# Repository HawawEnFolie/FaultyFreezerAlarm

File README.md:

# Faulty Ultralow-temperature Freezer Alarm

## ⟪ DESCRIPTION ⟫

This repository contains the source code and documentation for a critical telemetry embedded system. Developed during the first year of the BTS CIEL ER program to meet the needs of the UPPA (University de Pau et des Pays de l'Adour) microbiology laboratories, this system monitors the temperature of ultra-low temperature freezers in real time. If the temperature crosses a critical threshold, here -65°C, the system triggers an immediate SMS alert via a 4G LTE cellular network to designated rsearchers so as to reduce as much as possible the time where samples are not correctly frozen.

## ⟪ FEATURES ⟫

**▰ High-Precision Acquisition ⪢** Temperature reading every 10 minutes via an industrial PT100 probe and a MAX31865 amplifier (SPI communication).

**▰ Cellular Connectivity ⪢** Automated messages sent over the mobile data network directly to a WhatsApp group using an HTTP API gateway on a SIMCom A7670E module

**▰ Anti-Spam Logic ⪢** The system includes a software lock to send only one SMS when the threshold is crossed, automatically resetting once the temperature stabilizes below a set level, so as not a flood the target phones with multiple SMS.

**▰ Local Monitoring ⪢** Real-time display of readings and network status on the serial monitor with integrated DEBUG mode as well as screen to show live info about the PT100.

**▰ Ambient Temperature Tracking ⪢** Continuous measurement of the ambient room temperature utilizing a TMP102 sensor.

**▰ Local Alerts & Interface ⪢** An integrated buzzer for immediate audible alarms and an SSD1315 OLED display equipped with 4 integrated buttons for local navigation and control.

## ⟪ HARDWARE REQUIREMENTS ⟫

**▰ Microcontroller & Modem ⪢** LilyGo T-A7670E development board (Based on an ESP32-WROVER with an integrated 4G LTE modem).

**▰ RTD Amplifier ⪢** Adafruit MAX31865 module.

**▰ Sensor ⪢** PT100 temperature probe with 4 wires (can be configured for 2 and 3 wires as well).

**▰ Additional Peripherals ⪢** TMP102 ambient temperature sensor, alert buzzer, and an SSD1315 OLED display module with 4 built-in buttons.

**▰ Power & Connectivity ⪢** Active SIM card (with SMS plan) and suitable power supply for the LilyGo board.

## ⟪ SOFTWARE REQUIREMENTS ⟫

**▰ IDE ⪢** Visual Studio Code with the PlatformIO extension.

**▰ Framework ⪢** Arduino (C++).

## [ Dependencies & Libraries ]

**▰** Adafruit MAX31865 library (Handling of the sensor's analog-to-digital conversion).

**▰** TinyGSM (Seamless handling of AT commands and communication with the SIMCom modem).

## ⟪ LICENSE ⟫
The source code of this project is licensed under **GPLv3**.
The hardware design files (Schematics, PCB, 3D models) are licensed under **CERN-OHL-S v2**.
See the LICENSE and cern_ohl_s_v2.txt files for more details.

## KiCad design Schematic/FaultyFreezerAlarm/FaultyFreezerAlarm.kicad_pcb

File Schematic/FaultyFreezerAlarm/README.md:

# Schematics & PCB

## 《 DESCRIPTION 》

This repository contains all the hardware design files for the electronic board created as part of this project. 

This project involves the design, schematic capture, and routing of a printed circuit board (PCB) meeting the specifications of the system requirements.

## 《 TECHNICAL SPECIFICATIONS 》

▰ **CAD Software** ➢ KiCad 9.0.

▰ **Design Rules** ➢ Default track width: 20th (0.508 mm).

▰ **Layer Count** ➢ 1 layer (Bottom).

▰ **Main Components** ➢ LilyGo T-A7670E, Adafruit MAX31865, and a PT100 probe.

## 《 WIRING SCHEMATIC 》

## 《 PROJECT STRUCTURE 》

▰ **`*.kicad_pro`** ➢ Main KiCad project file.

▰ **`*.kicad_sch`** ➢ Electrical schematic file.

▰ **`*.kicad_pcb`** ➢ Printed circuit board routing file.

▰ **`/gerber/`** ➢ (Optional) Export files for board manufacturing.

## 《 HOW TO OPEN THE PROJECT 》

▰ **Step 1** ➢ Ensure you have **KiCad (version 9.0 or higher)** installed.

▰ **Step 2** ➢ Clone this repository or download the files.

▰ **Step 3** ➢ Launch KiCad and open the `.kicad_pro` file located in the root directory.

## 《 AUTHOR 》

**Robin Paniagua Desclaux**
*Student in BTS CIEL ER (1st year)*

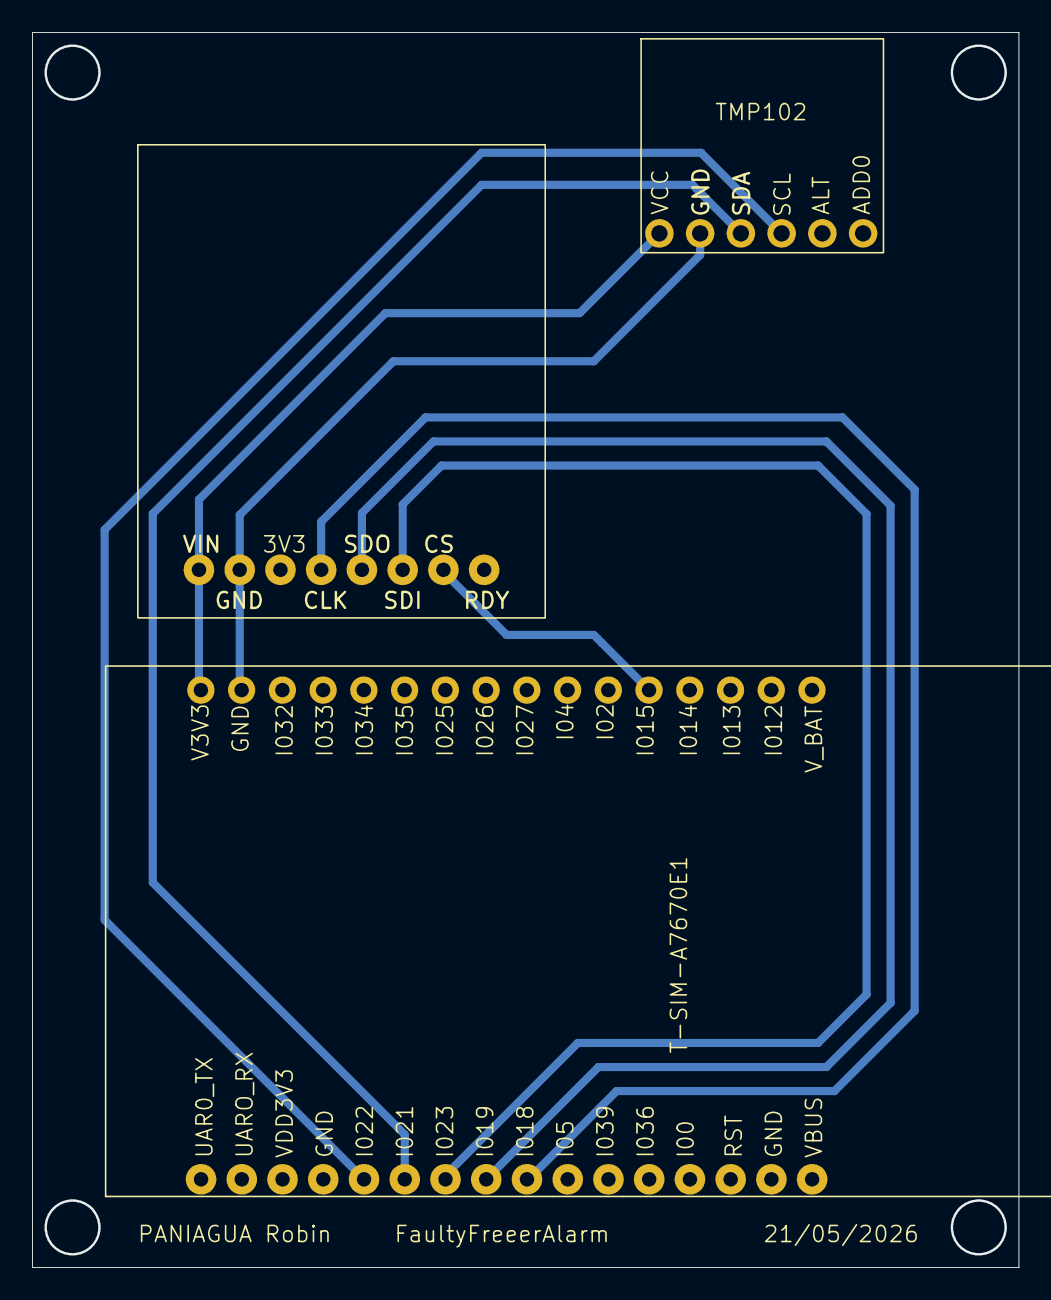
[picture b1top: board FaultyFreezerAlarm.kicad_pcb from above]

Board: 2 copper layers, 61.5 x 77.0 mm, 3 parts (0 on the bottom side), 8 nets.

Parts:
MAX31865: MAX31865
T-SIM-A7670E1: T-SIM-A7670E
TMP102: TMP102

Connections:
GNDPWR: MAX31865.2 (GND), T-SIM-A7670E1.10 (GND), TMP102.2 (GND), TMP102.6 (ADDO)
unnamed: MAX31865.4 (CLK), T-SIM-A7670E1.18 (I018)
unnamed: MAX31865.7 (CS), T-SIM-A7670E1.15 (I015)
unnamed: MAX31865.6 (SDI), T-SIM-A7670E1.23 (I023)
unnamed: MAX31865.5 (SDO), T-SIM-A7670E1.19 (I019)
unnamed: T-SIM-A7670E1.22 (I022), TMP102.4 (SCL)
unnamed: T-SIM-A7670E1.21 (I021), TMP102.3 (SDA)
VCC: MAX31865.1 (VIN), T-SIM-A7670E1.11 (V3V3), TMP102.1 (VCC)

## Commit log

2026-05-19 Remove wiring diagram for ESP32 connections
    Removed wiring diagram section for ESP32 pinout.
2026-05-19 Update README.md
    New, better and more visual version of the README.md
2026-05-20 Create v1
2026-05-21 Update layer count and component list in Readme
2026-05-21 Rename Readme to Readme.md
2026-05-21 Create Version1
2026-05-21 Create a
2026-05-28 Refactor main.cpp for improved modem and alert logic
2026-05-29 Update README.md formatting and content structure
2026-06-02 Replace wiring schematic image in README
    Updated wiring schematic image for version 2.0.
2026-06-18 Replace GPL with custom license details
    Updated license information and removed the GNU General Public License text.
2026-06-18 Add LICENSE file for FaultyFreezerAlarm
    Added LICENSE file for FaultyFreezerAlarm project.
2026-06-18 Include LICENSE section in README.md
    Add licensing information for source code and hardware design files.
2026-06-18 Rename LICENSE to cern_ohl_s_v2.txt
2026-06-18 Create README for FFA Terminal application
    Added README.md for FFA Terminal application detailing features, software requirements, and licensing.
2026-06-18 Update LICENSE to include GNU GPL version 3
    Replaced project description with GNU General Public License text.
2026-06-18 Update license information to GPLv3
2026-06-18 Add CERN Open Hardware Licence Version 2 document
2026-06-23 Revise cellular connectivity feature description
    Updated the description of cellular connectivity feature to reflect the use of WhatsApp instead of SMS.
